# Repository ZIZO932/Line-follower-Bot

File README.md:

# Line Follower Bot

This is my competition line follower. Our team won first place in the seniors line follower category at TechnoXian Egypt and qualified for the World Cup in Malaysia. I worked on the custom PCB, mechanical design, assembly, and tuning.

## What I wanted to learn

I wanted to understand PID control properly, so I researched existing line followers and built my own version around an Arduino Pro Mini and a QTR-8RC sensor array.

The robot uses the sensor array to read the line and adjust the two motors. I also added an HC-05 Bluetooth module so I could change tuning values without uploading the code again every time.

## Hardware

- Arduino Pro Mini
- QTR-8RC eight-channel reflectance sensor array
- Dual motor driver, listed as DRV8835 in the original design notes
- HC-05 Bluetooth module
- 7.4 V battery and 5 V regulator
- Power switch and buttons
- Custom PCB and printed chassis, sensor mount, and battery support

The original parts list names a DRV8835, but its supplier link points to a DRV8833. Check the circuit files and the board you're using before treating that link as an exact replacement.

## How the build went

I started with the schematic, then moved to the PCB. There were footprint issues to fix before routing, and I added mounting holes so the board could screw into the body.

I designed the chassis around the electronics, keeping the sensor low and aligned with the ground and giving the battery its own support. Before the PCB arrived, I tested the controller, Bluetooth connection, motor directions, sensor channels, and regulator on a breadboard. That caught some wiring mistakes early.

Once the board arrived, I soldered it, checked for bridges and wrong orientations, and checked power and ground with a multimeter before powering it up.

## CAD

## Tuning and demo

The values recorded in my build notes were `Kp = 0.02`, `Ki = 0`, and `Kd = 0.6`. Those belong to this setup and aren't universal settings for another robot.

[Watch the S-shaped track demo](https://youtu.be/TAyl4BceC5A) or open the [uploaded video](Demo%20video.mp4).

The sketch currently uploaded in `Firmware/` is a motor direction test. Despite its filename, it isn't the full PID or Bluetooth tuning firmware.

## Parts list

These are the original component estimates and supplier links. They aren't current prices or a complete cost for the whole robot.

|Component                                          |Store                |Qty|Unit Price (EGP)|Total (EGP)                    |Total (USD approx)|Link                                                                                                                                     |
|---------------------------------------------------|---------------------|---|----------------|-------------------------------|------------------|-----------------------------------------------------------------------------------------------------------------------------------------|
|Arduino Pro Mini 328 5V/16MHz                      |RAM Electronics      |1  |250             |250                            |4.98              |https://www.ram-e-shop.com/shop/arduino-mini-pro-arduino-pro-mini-328-5v-16mhz-7180                                                      |
|DRV8835 Dual Motor Driver                          |Makers Electronics   |1  |180             |180                            |3.59              |https://makerselectronics.com/product/drv8833-2-channel-dc-motor-driver/?srsltid=AfmBOopl0AXVi_7erC0TRuiovgie-HcAb31S7vhGDk1mQixUt8-UI5Q2|
|QTR-8RC 8 Channel Line Sensor Array                |Micro Ohm Electronics|1  |135             |135                            |2.69              |https://microohm-eg.com/qtr-8rc-8-channel-line-tracker-reflectance-sensor-array/                                                         |
|HC-05 Bluetooth Module (6 pin)                     |RAM Electronics      |1  |200             |200                            |3.98              |https://www.ram-e-shop.com/shop/kit-bluetooth-hc05-normal-hc-05-bluetooth-module-normal-6674                                             |
|7.4V Li-ion Battery Pack 2S-1P 1000mAh w/ BMS + JST|Makers Electronics   |1  |210             |210                            |4.18              |https://makerselectronics.com/product/rechargeable-li-ion-battery-pack-7-4v-2s-1pbms-1000mah-18650-with-jst-cable/                       |
|L7805CV Voltage Regulator 5V/1A TO-220             |Micro Ohm Electronics|1  |6               |6                              |0.12              |https://microohm-eg.com/product/7805-regulator-ic/                                                                                       |
|DPDT Slide Power Switch (ON/ON 6 pin)              |Micro Ohm Electronics|1  |10              |10                             |0.2               |https://microohm-eg.com/on-on-switch-6-pin-pcb-mounted-22mm-dpdt-slide-switch/                                                           |
|Tactile Push Button 12x12x12mm                     |Micro Ohm Electronics|1  |3.5             |3.5                            |0.07              |https://microohm-eg.com/press-12x12x12mm-push-button-switch-4-pin/                                                                       |
|TOTAL                                              |                     |   |                |994.50 (incl. DRV8835 estimate)|19.81             |                                                                                                                                         |

## Zine

[Open the PDF](Magazine/Magazine%20of%20Line%20follower%20bot.pdf).

## Files

- [CAD](CAD/) — assembly and STEP model
- [Individual SolidWorks parts](3D%20model%20source/)
- [Schematic, PCB, and Gerbers](Schematic%20and%20PCB/)
- [Motor test sketch](Firmware/Final_code_i_hope.ino)
- [BOM](BOM.csv)
- [Build journal](line-follower-bot-journal.md)

I'm also planning a new standalone ATmega328P design: [Line-E](https://github.com/ZIZO932/Line-E).

Made by Ziad, or Zizo if you know me from Hack Club.

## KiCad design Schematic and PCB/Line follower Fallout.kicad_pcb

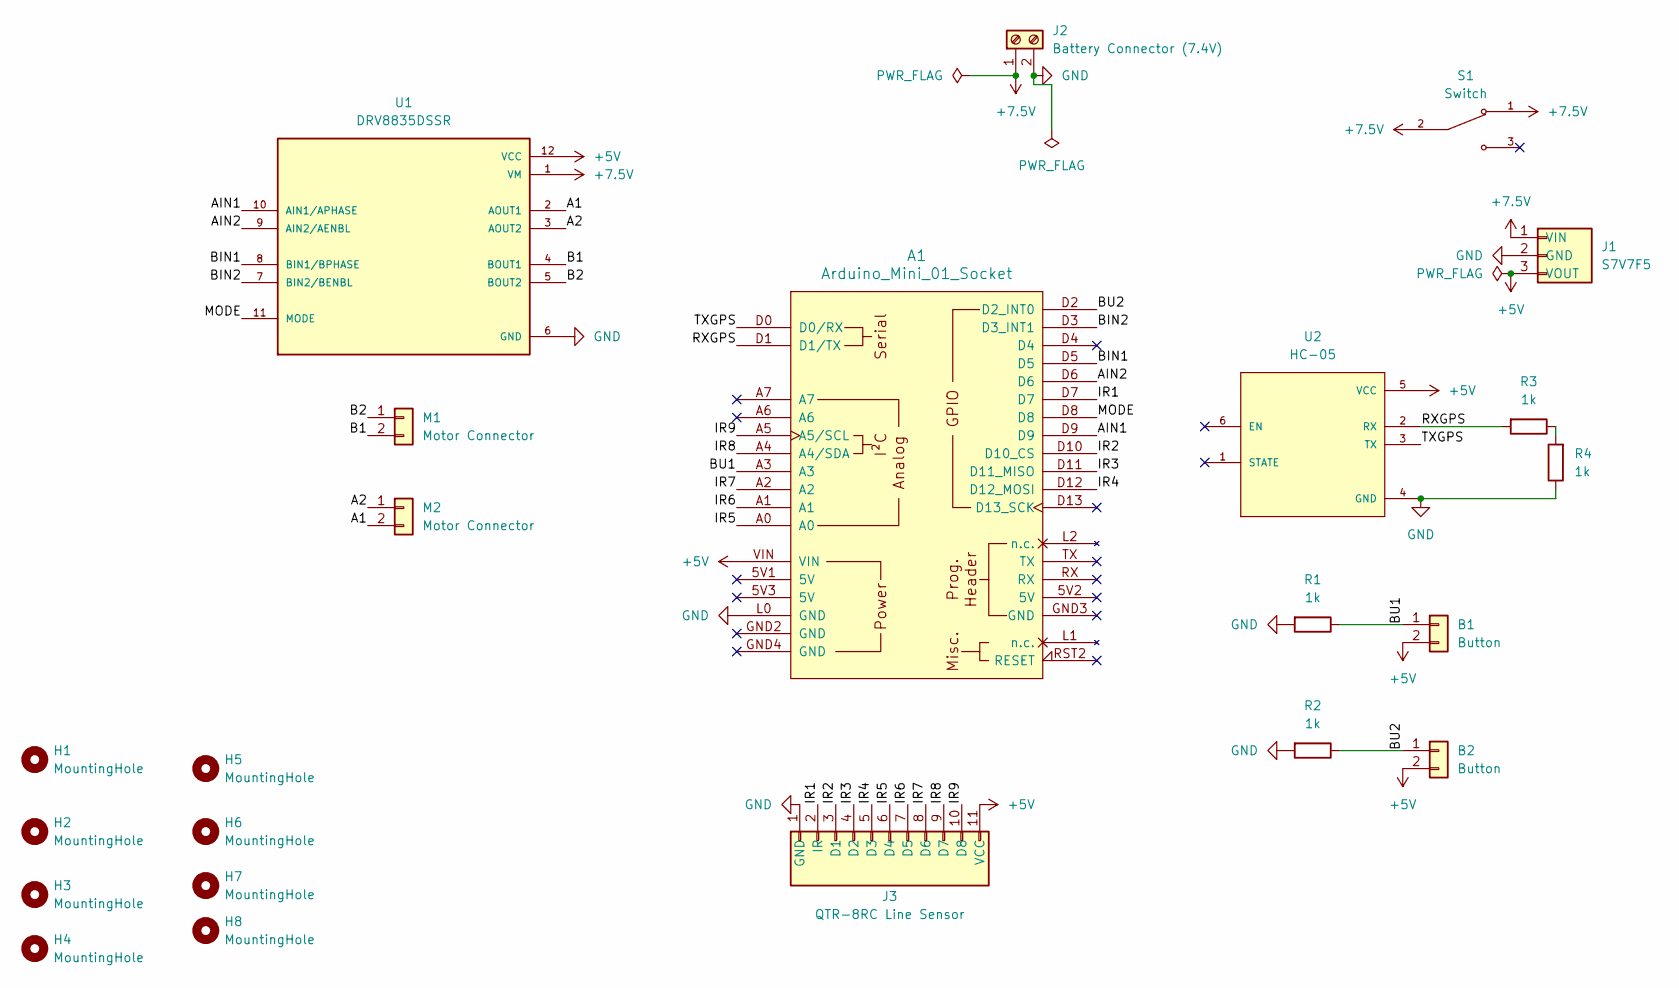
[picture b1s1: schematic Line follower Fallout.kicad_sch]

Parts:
A1: Arduino_Mini_01_Socket; Arduino_Mini_Socket
B1, B2: Button; SW_PUSH_6mm_H4.3mm
H1, H2, H3, H4, H5, H6, H7, H8: MountingHole; MountingHole_2.2mm_M2_DIN965
J1: S7V7F5; PinHeader_1x03_P2.54mm_Vertical
J2: Battery Connector (7.4V); TerminalBlock_Phoenix_MKDS-1,5-2-5.08_1x02_P5.08mm_Horizont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
J3: QTR-8RC Line Sensor; PinHeader_1x11_P2.54mm_Vertical
M1, M2: Motor Connector; JST_XH_B2B-XH-A_1x02_P2.50mm_Vertical
R1, R2, R3, R4: 1k; R_Axial_DIN0207_L6.3mm_D2.5mm_P10.16mm_Horizontal
S1: Switch; SW_MINI-SPDT-SW; PARTREV C
U1: DRV8835DSSR; DIP-14_W10.16mm; PARTREV H
U2: HC-05; MODULE_ZC142200; PARTREV N/A

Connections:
+5V: A1.VIN, B1.2, B2.2, J1.3 (VOUT), J3.11 (VCC), U1.12 (VCC), U2.5 (VCC)
+7.5V: J1.1 (VIN), J2.1, S1.1, S1.2, U1.1 (VM)
/A1: M2.2, U1.2 (AOUT1)
/A2: M2.1, U1.3 (AOUT2)
/AIN1: A1.D9, U1.10 (AIN1/APHASE)
/AIN2: A1.D6, U1.9 (AIN2/AENBL)
/B1: M1.2, U1.4 (BOUT1)
/B2: M1.1, U1.5 (BOUT2)
/BIN1: A1.D5, U1.8 (BIN1/BPHASE)
/BIN2: A1.D3 (D3_INT1), U1.7 (BIN2/BENBL)
/BU1: A1.A3, B1.1, R1.1
/BU2: A1.D2 (D2_INT0), B2.1, R2.1
/IR1: A1.D7, J3.2 (IR)
/IR2: A1.D10 (D10_CS), J3.3 (D1)
/IR3: A1.D11 (D11_MISO), J3.4 (D2)
/IR4: A1.D12 (D12_MOSI), J3.5 (D3)
/IR5: A1.A0, J3.6 (D4)
/IR6: A1.A1, J3.7 (D5)
/IR7: A1.A2, J3.8 (D6)
/IR8: A1.A4 (A4/SDA), J3.9 (D7)
/IR9: A1.A5 (A5/SCL), J3.10 (D8)
/MODE: A1.D8, U1.11 (MODE)
/RXGPS: A1.D1 (D1/TX), R3.2, U2.2 (RX)
/TXGPS: A1.D0 (D0/RX), U2.3 (TX)
GND: A1.L0 (GND), J1.2 (GND), J2.2, J3.1 (GND), R1.2, R2.2, R4.1, U1.6 (GND), U1.13 (GND), U2.4 (GND)
unnamed: R3.1, R4.2

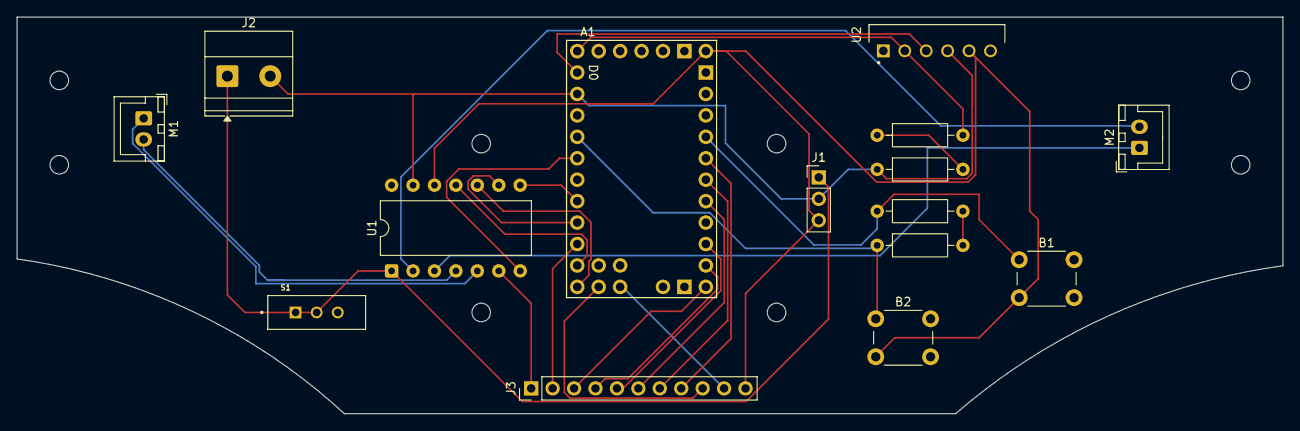
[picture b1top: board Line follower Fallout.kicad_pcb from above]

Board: 2 copper layers, 150.0 x 47.0 mm, 23 parts (0 on the bottom side), 26 nets.

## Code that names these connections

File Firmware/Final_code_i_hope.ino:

int ain1 = 9;
int ain2 = 6;
int bin1 = 5;
int bin2 = 3;

void setup() {
  pinMode(ain1, OUTPUT);
  pinMode(ain2, OUTPUT);
  pinMode(bin1, OUTPUT);
  pinMode(bin2, OUTPUT);
}

void loop() {
  // Test 1: Motor A forward
  analogWrite(ain1, 150);
  digitalWrite(ain2, LOW);
  digitalWrite(bin1, LOW);
  digitalWrite(bin2, LOW);
  delay(2000);

  // Stop
  digitalWrite(ain1, LOW);
  digitalWrite(ain2, LOW);
  digitalWrite(bin1, LOW);
  digitalWrite(bin2, LOW);
  delay(1000);

  // Test 2: Motor A backward
  digitalWrite(ain1, LOW);
  analogWrite(ain2, 150);
  digitalWrite(bin1, LOW);
  digitalWrite(bin2, LOW);
  delay(2000);

  // Stop
  digitalWrite(ain1, LOW);
  digitalWrite(ain2, LOW);
  digitalWrite(bin1, LOW);
  digitalWrite(bin2, LOW);
  delay(1000);

  // Test 3: Motor B forward
  digitalWrite(ain1, LOW);
  digitalWrite(ain2, LOW);
  analogWrite(bin1, 150);
  digitalWrite(bin2, LOW);
  delay(2000);

  // Stop
  digitalWrite(ain1, LOW);
  digitalWrite(ain2, LOW);
  digitalWrite(bin1, LOW);
  digitalWrite(bin2, LOW);
  delay(1000);

  // Test 4: Motor B backward
  digitalWrite(ain1, LOW);
  digitalWrite(ain2, LOW);
  digitalWrite(bin1, LOW);
  analogWrite(bin2, 150);
  delay(2000);

  // Stop
  digitalWrite(ain1, LOW);
  digitalWrite(ain2, LOW);
  digitalWrite(bin1, LOW);
  digitalWrite(bin2, LOW);
  delay(1000);
}
